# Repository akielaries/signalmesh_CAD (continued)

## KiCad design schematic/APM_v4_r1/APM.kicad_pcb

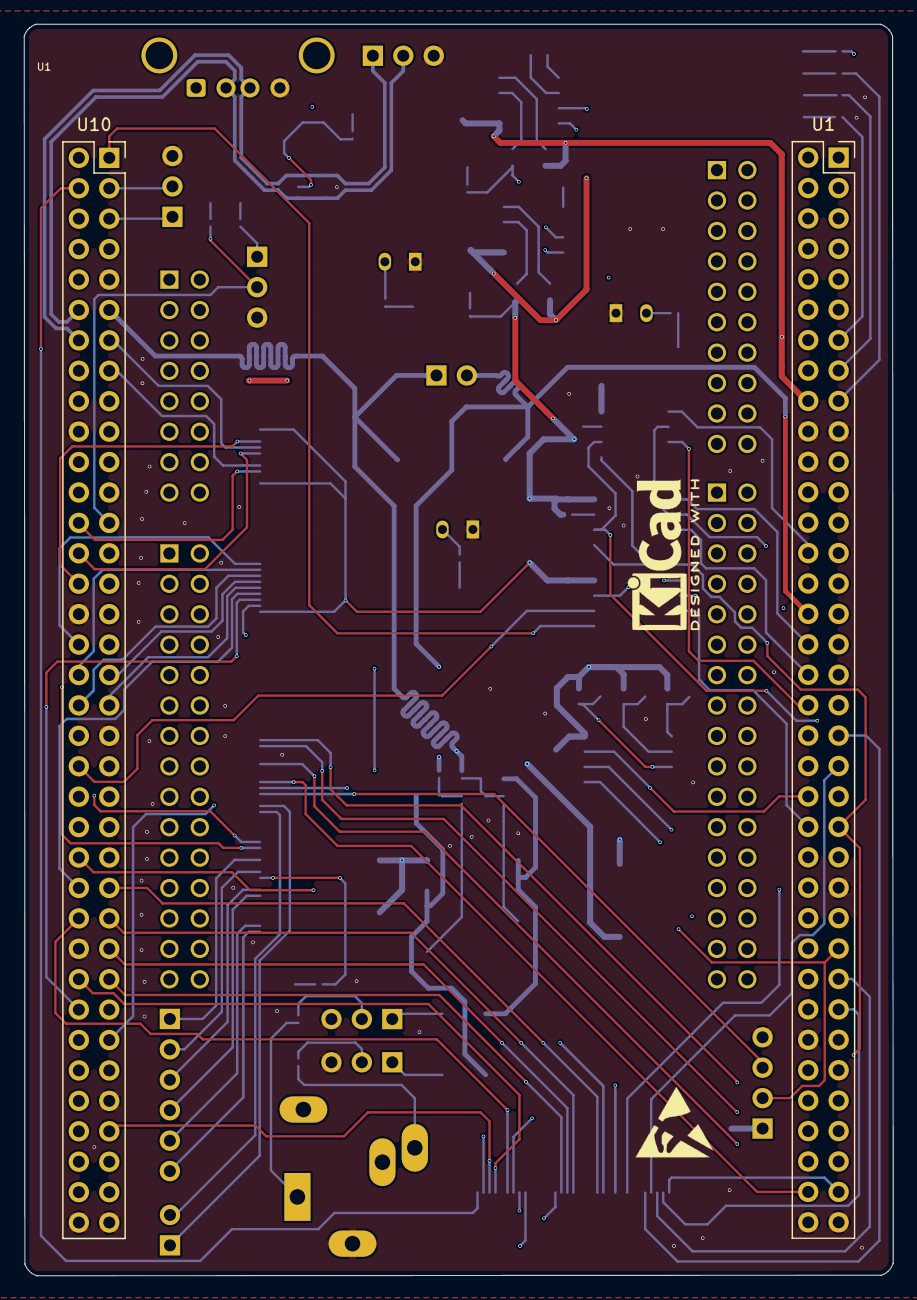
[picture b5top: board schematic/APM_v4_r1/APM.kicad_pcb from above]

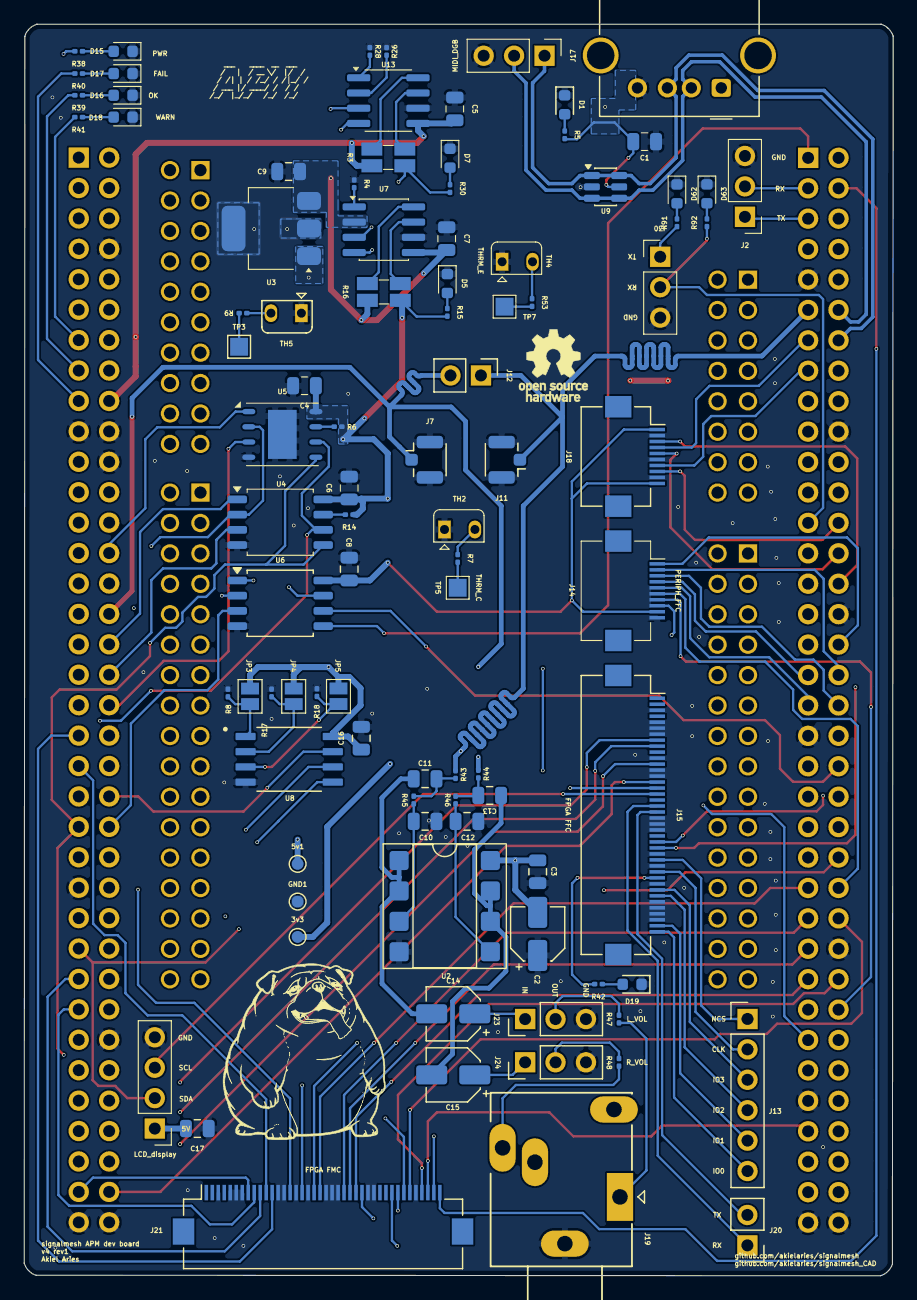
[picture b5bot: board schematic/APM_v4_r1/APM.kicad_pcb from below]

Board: 4 copper layers, 72.5 x 104.5 mm, 97 parts (94 on the bottom side), 119 nets.

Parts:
3v3: 3v3; TestPoint_Pad_D1.0mm
5v1: 5v; TestPoint_Pad_D1.0mm
C1: 22pf; C_0805_2012Metric
C2, C14, C15: 10uF; CP_Elec_4x3
C3, C4, C6, C8, C9, C16, C17: 100nF; C_0805_2012Metric
C5, C7: 0.1uf; C_0805_2012Metric
C10, C12: 2.2nF; C_0805_2012Metric
C11, C13: 4.7nF; C_0805_2012Metric
D1, D5, D7: LED_PWR; LED_0603_1608Metric
D15: PWR; LED_0603_1608Metric
D16: OK; LED_0603_1608Metric
D17: FAIL; LED_0603_1608Metric
D18: WARN; LED_0603_1608Metric
D19: FPGA_PWR; LED_0603_1608Metric
D62: TXD; LED_0603_1608Metric
D63: RXD; LED_0603_1608Metric
GND1: GND; TestPoint_Pad_D1.0mm
J2: CAN; PinHeader_1x03_P2.54mm_Vertical
J4: LCD_display; PinHeader_1x04_P2.54mm_Vertical
J7: DAC_R_PRB; U.FL_Hirose_U.FL-R-SMT-1_Vertical
J11: DAC_L_PRB; U.FL_Hirose_U.FL-R-SMT-1_Vertical
J12: Conn_01x02; PinHeader_1x02_P2.54mm_Vertical
J13: Conn_01x06; PinHeader_1x06_P2.54mm_Vertical
J14: POT_FFC; Hirose_FH12-10S-0.5SH_1x10-1MP_P0.50mm_Horizontal
J15: FPGA FFC; Hirose_FH12-40S-0.5SH_1x40-1MP_P0.50mm_Horizontal
J16: USB_A_FEMALE; USB_A_Molex_67643_Horizontal
J17: MIDI_DGB; PinHeader_1x03_P2.54mm_Vertical
J18: CTRL_FFC; Hirose_FH12-10S-0.5SH_1x10-1MP_P0.50mm_Horizontal
J19: AudioPlug3; Jack_3.5mm_Ledino_KB3SPRS_Horizontal
J20: FPGA_UART; PinHeader_1x02_P2.54mm_Vertical
J21: FPGA FMC; Hirose_FH12-40S-0.5SH_1x40-1MP_P0.50mm_Horizontal
J23: VOL_L_CTRL; PinHeader_1x03_P2.54mm_Vertical
J24: VOL_R_CTRL; PinHeader_1x03_P2.54mm_Vertical
J30: UART_DEBUG; PinHeader_1x03_P2.54mm_Vertical
JP3: A0; SolderJumper-2_P1.3mm_Open_Pad1.0x1.5mm
JP4: A1; SolderJumper-2_P1.3mm_Open_Pad1.0x1.5mm
JP5: A2; SolderJumper-2_P1.3mm_Open_Pad1.0x1.5mm
R3, R16: 0.1; R_Shunt_Ohmite_LVK12
R4, R6, R7, R8, R9, R14, R17, R18, R26, R28, R53: 10k; R_0201_0603Metric
R5, R15, R30, R39, R40, R41, R42, R91, R92: 300; R_0201_0603Metric
R38: 1.2k; R_0201_0603Metric
R43, R44, R45, R46: 2.4k; R_0201_0603Metric
R47, R48: 47; R_0201_0603Metric
TH2, TH4, TH5: 10k; Heraeus_TO-92-2
TP3: THRM_A; TestPoint_Pad_1.5x1.5mm
TP5: THRM_C; TestPoint_Pad_1.5x1.5mm
TP7: THRM_E; TestPoint_Pad_1.5x1.5mm
U1: NUCLEO-H753ZI; ST_Morpho_and_Zio_Connectors_144_STLink
U1#2, U10: PinSocket_2x36_P2.54mm_Vertical
U2: OPA1678; DIP-8_W7.62mm_SMDSocket_SmallPads
U3: LT1963AxST-3.3; SOT-223-3_TabPin2
U4, U6: W25Q128JVS; SOIC-8_5.3x5.3mm_P1.27mm
U5: MR25H40; DFN-S-8-1EP_6x5mm_P1.27mm
U7, U13: INA219AxD; SOIC-8_3.9x4.9mm_P1.27mm
U8: 24LC1025-I_P; SOIC127P794X202-8N
U9: USBLC6-2SC6; SOT-23-6

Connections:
3V3_APM: 3v3.1 (1_1), C4.1, C6.1, C8.1, C16.1, J14.9, J18.1, J18.10, JP3.2 (B), JP4.2 (B), JP5.2 (B), R6.1, R14.1, R15.2, R16.4, U4.8 (VCC), U5.8 (VDD), U6.8 (VCC), U8.8 (VCC)
3V3_LDO: C7.2, C9.1, R16.1, U3.3 (OUT), U7.2 (A0), U7.5 (VS)
5V_APM: C1.2, C2.2, C3.2, C17.2, J4.1, J16.1 (VBUS), R3.4, R5.2, R30.2, R38.2, U2.8 (V+), U3.1 (IN), U9.5 (VBUS)
5V_APM_MCU: 5v1.1 (1_1), C5.2, R3.1, U1#2.18 (5V), U13.5 (VS)
/ADC_POT_1: J14.1, U10.34 (PC4)
/ADC_POT_2: J14.2, U10.36 (PF5)
/ADC_POT_3: J14.3, U10.38 (PF4)
/ADC_POT_4: J14.4, U10.35 (PA2)
/ADC_POT_5: J14.5, U10.37 (PA3)
/ADC_POT_6: J14.6, U10.50 (PF14)
/ADC_POT_7: J14.7, U10.58 (PF3)
/ADC_POT_8: J14.8, U10.59 (PF12)
/APM_CAN_RD: J2.2, U10.3 (PB8)
/APM_CAN_TD: J2.1, U10.5 (PB9)
/APM_DBG_RX: J30.2, R92.1, U10.25 (PB10)
/APM_DBG_TX: J30.1, R91.1, U10.21 (PA9)
/APM_EEPROM_EN: U1#2.44 (PG3), U8.7 (WP)
/APM_FMC_DA0: J21.33, U10.46 (PD14)
/APM_FMC_DA1: J21.34, U10.48 (PD15)
/APM_FMC_DA2: J21.9, U1#2.57 (PD0)
/APM_FMC_DA3: J21.10, U1#2.55 (PD1)
/APM_FMC_DA4: J21.32, U10.44 (PE7)
/APM_FMC_DA5: J21.27, U10.40 (PE8)
/APM_FMC_DA6: J21.35, U10.52 (PE9)
/APM_FMC_DA7: J21.19, U10.47 (PE10)
/APM_FMC_DA8: J21.37, U10.56 (PE11)
/APM_FMC_DA9: J21.20, U10.49 (PE12)
/APM_FMC_DA10: J21.26, U10.55 (PE13)
/APM_FMC_DA11: J21.24, U10.51 (PE14)
/APM_FMC_DA12: J21.25, U10.53 (PE15)
/APM_FMC_DA13: J21.39, U10.10 (PD8)
/APM_FMC_DA14: J21.8, U1#2.69 (PD9)
/APM_FMC_DA15: J21.38, U10.65 (PD10)
/APM_FMC_NE1: J21.17, U10.19 (PC7)
/APM_FMC_NL: J21.15, U1#2.21 (PB7)
/APM_FMC_NOE: J21.12, U1#2.39 (PD4)
/APM_FMC_NWAIT: J21.40, U10.4 (PC6)
/APM_FMC_NWE: J21.11, U1#2.41 (PD5)
/APM_FPGA_UART_RX: J15.25, U10.23 (PA8)
/APM_FPGA_UART_TX: J15.26, U10.31 (PB3)
/APM_I2C2_SCL: J4.3, J15.17, U1#2.51 (PF1), U7.4 (SCL), U8.6 (SCL), U13.4 (SCL)
/APM_I2C2_SDA: J4.2, J15.16, U1#2.53 (PF0), U7.3 (SDA), U8.5 (SDA), U13.3 (SDA)
/APM_LED_FAIL: R41.2, U1#2.13 (PA13)
/APM_LED_OK: R39.2, U1#2.15 (PA14)
/APM_LED_WARN: R40.2, U1#2.17 (PA15)
/APM_MRAM_EN: U1#2.38 (PC0), U5.3 (~WP)
/APM_SPI1_CS: J15.12, U1#2.66 (PG10)
/APM_SPI1_MISO: J15.9, U1#2.63 (PG9), U4.2 (DO/IO_{1}), U5.2 (SO)
/APM_SPI1_MOSI: J15.8, U1#2.45 (PD7), U4.5 (DI/IO_{0}), U5.5 (SI)
/APM_SPI1_SCK: J15.15, U1#2.70 (PG11), U4.6 (CLK), U5.6 (SCK)
/APM_SPI2_MISO: J18.5, U10.28 (PB14)
/APM_SPI2_MOSI: J18.8, U10.26 (PB15)
/APM_SPI2_SCK: J18.3, U10.30 (PB13)
/APM_SPIFLASH_EN: U1#2.36 (PC1), U4.3 (~WP/IO_{2})
/AUDIO_APM/OUT_L: J23.2, R47.2
/AUDIO_APM/OUT_R: J24.2, R48.2
/AUDIO_APM/VOL_L_IN: C14.1, J23.1
/AUDIO_APM/VOL_R_IN: C15.1, J24.1
/DAC_1-1_R: J7.1 (In), J12.2, R44.1, U1#2.32 (PA4)
/DAC_1-2_L: J11.1 (In), J12.1, R43.1, U10.11 (PA5)
/FPGA_UART_RX: J15.20, J20.2
/FPGA_UART_TX: J15.19, J20.1
/MIDI_FS_D+: J16.3 (D+), J17.1, U9.1 (I/O1), U9.6 (I/O1), U10.14 (PA11)
/MIDI_FS_D-: J16.2 (D-), J17.2, U9.3 (I/O2), U9.4 (I/O2), U10.12 (PA12)
/NC: U1#2.25 (PC14), U1#2.27 (PC15), U1#2.29 (PH0)
/QSPI1_D0: U6.5 (DI/IO_{0}), U10.1 (PC9)
/QSPI1_D1: U1#2.1 (PC10), U6.2 (DO/IO_{1})
/QSPI1_D2: U1#2.46 (PE2), U6.3 (~WP/IO_{2})
/QSPI1_D3: U1#2.30 (PA1), U6.7 (~HOLD/~RESET/IO_{3})
/QSPI1_NCS: U6.1 (~CS), U10.70 (PG6)
/QSPI_CLK: J13.2, J15.30
/QSPI_IO_0: J13.6, J15.40
/QSPI_IO_1: J13.5, J15.39
/QSPI_IO_2: J13.4, J15.34
/QSPI_IO_3: J13.3, J15.33
/QSPI_NCS: J13.1, J15.28
/QSPI_SCK2: U6.6 (CLK), U10.42 (PF10)
/SPIFLASH_CS: U1#2.34 (PB0), U4.1 (~CS)
/SPIMRAM_CS: U1#2.28 (PA0), U5.1 (~CS)
/SR_GPIO1: J18.4, U10.13 (PA6)
/SR_GPIO2: J18.7, U10.15 (PA7)
/THRM_A: R9.2, TP3.1 (1_1)
/THRM_C: R7.2, TP5.1 (1_1)
/THRM_E: R53.2, TP7.1 (1_1)
DAC_L_OUT: C11.1, C14.2, U2.1, U2.2 (-)
DAC_R_OUT: C13.1, C15.2, U2.6 (-), U2.7
FPGA_3V3_OUT1: J15.31, R42.2
GND: C1.1, C2.1, C3.1, C4.2, C5.1, C6.2, C7.1, C8.2, C9.2, C10.1, C12.1, C16.2, C17.1, D1.1 (K), D5.1 (K), D7.1 (K), D15.1 (K), D16.1 (K), D17.1 (K), D18.1 (K), D19.1 (K), D62.1 (K), D63.1 (K), GND1.1 (1_1), J2.3, J4.4, J7.2 (Ext), J11.2 (Ext), J14.10, J15.3, J15.5, J15.6, J15.7, J15.11, J15.13, J15.14, J15.21, J15.22, J15.23, J15.27, J15.29, J15.32, J15.35, J15.36, J15.37, J15.38, J16.4 (GND), J17.3, J18.2, J18.6, J18.9, J19.S, J21.3, J21.5, J21.6, J21.7, J21.13, J21.14, J21.16, J21.18, J21.21, J21.22, J21.23, J21.28, J21.29, J21.36, J23.3, J24.3, J30.3, R4.1, R8.2, R17.2, R18.2, R26.1, R28.1, TH2.1, TH4.1, TH5.1, U1#2.8 (GND_CN11), U1#2.19 (GND_CN11), U1#2.20 (GND_CN11), U1#2.22 (GND_CN11), U1#2.49 (GND_CN11), U1#2.60 (GND_CN11), U1#2.71 (GND_CN11), U1#2.72 (GND_CN11), U2.4 (V-), U3.2 (GND), U4.4 (GND), U5.4 (VSS), U5.9 (PAD), U6.4 (GND), U7.6 (GND), U8.4 (VSS), U9.2 (GND), U10.9 (GND_CN12), U10.20 (GND_CN12), U10.32 (AGND_CN12), U10.39 (GND_CN12), U10.54 (GND_CN12), U10.63 (GND_CN12), U10.71 (GND_CN12), U10.72 (GND_CN12), U13.6 (GND)
unnamed: C11.2, R43.2, R45.1
unnamed: C13.2, R44.2, R46.1
unnamed: D1.2 (A), R5.1
unnamed: D5.2 (A), R15.1
unnamed: D7.2 (A), R30.1
unnamed: D15.2 (A), R38.1
unnamed: D16.2 (A), R39.1
unnamed: D17.2 (A), R40.1
unnamed: D18.2 (A), R41.1
unnamed: D19.2 (A), R42.1
unnamed: D62.2 (A), R91.2
unnamed: D63.2 (A), R92.2
unnamed: J19.R, R48.1
unnamed: J19.T, R47.1
unnamed: JP3.1 (A), R8.1, U8.1 (A0)
unnamed: JP4.1 (A), R17.1, U8.2 (A1)
unnamed: JP5.1 (A), R18.1, U8.3 (A2)
unnamed: R7.1, TH2.2
unnamed: R9.1, TH5.2
unnamed: R53.1, TH4.2
unnamed: C10.2, R45.2, U2.3 (+)
unnamed: C12.2, R46.2, U2.5 (+)
unnamed: R14.2, U4.7 (~HOLD/~RESET/IO_{3})
unnamed: R6.2, U5.7 (~HOLD)
unnamed: R4.2, U7.1 (A1)
unnamed: R16.2, U7.8 (IN+)
unnamed: R16.3, U7.7 (IN-)
unnamed: R26.2, U13.2 (A0)
unnamed: R28.2, U13.1 (A1)
unnamed: R3.2, U13.8 (IN+)
unnamed: R3.3, U13.7 (IN-)

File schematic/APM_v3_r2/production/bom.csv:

Designator,Footprint,Quantity,Value,LCSC Part #
C1,0805,1,22pf,
"C4, C6, C8",0805,3,100nF,
"C5, C7",0805,2,0.1uf,
"D1, D5, D7",0603,3,LED_PWR,
D15,0603,1,PWR,
D16,0603,1,OK,
D17,0603,1,FAIL,
D18,0603,1,WARN,
D19,0603,1,FPGA_PWR,
D62,0603,1,TXD,
D63,0603,1,RXD,
J1,PinHeader_1x03_P2.54mm_Vertical,1,ACM_CTRL,
J11,U.FL_Hirose_U.FL-R-SMT-1_Vertical,1,DAC_L_PRB,
J12,PinHeader_1x02_P2.54mm_Vertical,1,Conn_01x02,
J13,PinHeader_1x06_P2.54mm_Vertical,1,Conn_01x06,
J14,Hirose_FH12-10S-0.5SH_1x10-1MP_P0.50mm_Horizontal,1,PERIPH_FFC,
J15,Hirose_FH12-40S-0.5SH_1x40-1MP_P0.50mm_Horizontal,1,FPGA FFC,
J16,USB_A_Molex_67643_Horizontal,1,USB_A_FEMALE,
J17,PinHeader_1x03_P2.54mm_Vertical,1,MIDI_DGB,
J2,PinHeader_1x03_P2.54mm_Vertical,1,CAN,
J20,PinHeader_1x02_P2.54mm_Vertical,1,FPGA_UART,
J21,PinHeader_1x02_P2.54mm_Vertical,1,APM_FPGA_UART,
J3,PinHeader_1x03_P2.54mm_Vertical,1,7SDD_CTRL,
J30,PinHeader_1x03_P2.54mm_Vertical,1,UART_DEBUG,
J4,PinHeader_1x04_P2.54mm_Vertical,1,LCD_display,
J5,PinHeader_1x02_P2.54mm_Vertical,1,INTRPT,
J7,U.FL_Hirose_U.FL-R-SMT-1_Vertical,1,DAC_R_PRB,
"R14, R17, R18, R26, R28, R4, R53, R6, R7, R8, R9",0201,11,10k,
"R15, R30, R39, R40, R41, R42, R5, R91, R92",0201,9,300,
"R16, R3",R_Shunt_Ohmite_LVK12,2,0.1,
R38,0201,1,1.2k,
"TH2, TH4, TH5",Heraeus_TO-92-2,3,10k,
TP3,TestPoint_Pad_1.5x1.5mm,1,THRM_A,
TP5,TestPoint_Pad_1.5x1.5mm,1,THRM_C,
TP7,TestPoint_Pad_1.5x1.5mm,1,THRM_E,
U1_2,ST_Morpho_and_Zio_Connectors_144_STLink,1,NUCLEO-H753ZI,
"U1, U10",PinSocket_2x36_P2.54mm_Vertical,2,~,
"U13, U7",SOIC-8_3.9x4.9mm_P1.27mm,2,INA219AxD,
U3,SOT-223-3_TabPin2,1,LT1963AxST-3.3,
"U4, U6",SOIC-8_5.3x5.3mm_P1.27mm,2,W25Q128JVS,
U5,DFN-S-8-1EP_6x5mm_P1.27mm,1,MR25H40,
U8,DIP787W46P254L927H533Q8,1,24LC1025-I_P,
U9,SOT-23-6,1,USBLC6-2SC6,

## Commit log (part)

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2025-07-30 moving CAD files from signalmesh repo
2025-08-04 progress on creating APM board first
2025-08-20 progress on board sep
2025-08-29 replacing the nucleo part with generic headers!
2025-08-30 ready for fab?
2025-08-30 gerbers pt 1. part matching next
2025-08-30 jlcpcb files
2025-09-10 adding rev3 changes
2025-09-10 should be good for refab and actual layout. may need better BOM matching tho
2025-09-10 actually no. need to rework ADC lines and perhaps make a pinout to an adapter board for the potentiometers for control. could be 3-4 of them for now?
2025-09-11 gonna use a 10 pin FFC to connect to the actual peripheral board
2025-09-13 voltage divider
2025-09-13 this seems good enough
2025-09-14 uploaded to jlcpcb
2025-09-17 sent out for assembly
2025-09-22 starting 7sdd board
2025-09-24 hmmm
2025-09-26 readme update with mermaid diagram
2025-09-27 APM v3?
2025-09-28 more apm v3 edits. back to filter board?
2025-09-28 working on LPFs
2025-10-20 some changes needed for next version based on my recent testing on the new order. biggest issue is FFC connector seems off in routes, INA has bad pinouts?, and LEDs are bright as shit. should probabl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
2026-04-26 backups
2026-05-25 updating top v10. need to get 3v3 APM converged in schematic. routing is tricky right now. the components should be evenly laid out and have the NUCLEO pins be adjusted based on location
2026-05-26 i got orientation wrong big time
2026-05-26 more progress
2026-05-30 more routing
2026-06-13 ground planes on f and b cu
2026-06-14 getting APM V3 R1 made. starting R2
2026-06-15 fab v3 r2?
2026-06-15 saved fab files
2026-06-17 routed
2026-06-17 routing changes
2026-06-18 v4 with new FFC conn
2026-06-18 v4 routed with FPGA FMC
2026-06-22 adding APM v5 and ACM adapter board for 25K primer module
2026-06-22 trying to get ACM adpater board routed with debug USB C in absence of ofthe BL616C
2026-06-22 ACM module board routed
2026-06-23 add backside connector. fix front connector orientation
2026-06-23 figuring out FFC traces next
2026-06-25 getting ACM and APM schematics put together. tool for FMC pin mapping verif
2026-06-26 seems like everything is routed? off by 1 error for I2C FPGA pins fixed?
2026-06-26 adding renders and render script
2026-06-30 schematic for the oscillator board
2026-06-30 wiring things up
